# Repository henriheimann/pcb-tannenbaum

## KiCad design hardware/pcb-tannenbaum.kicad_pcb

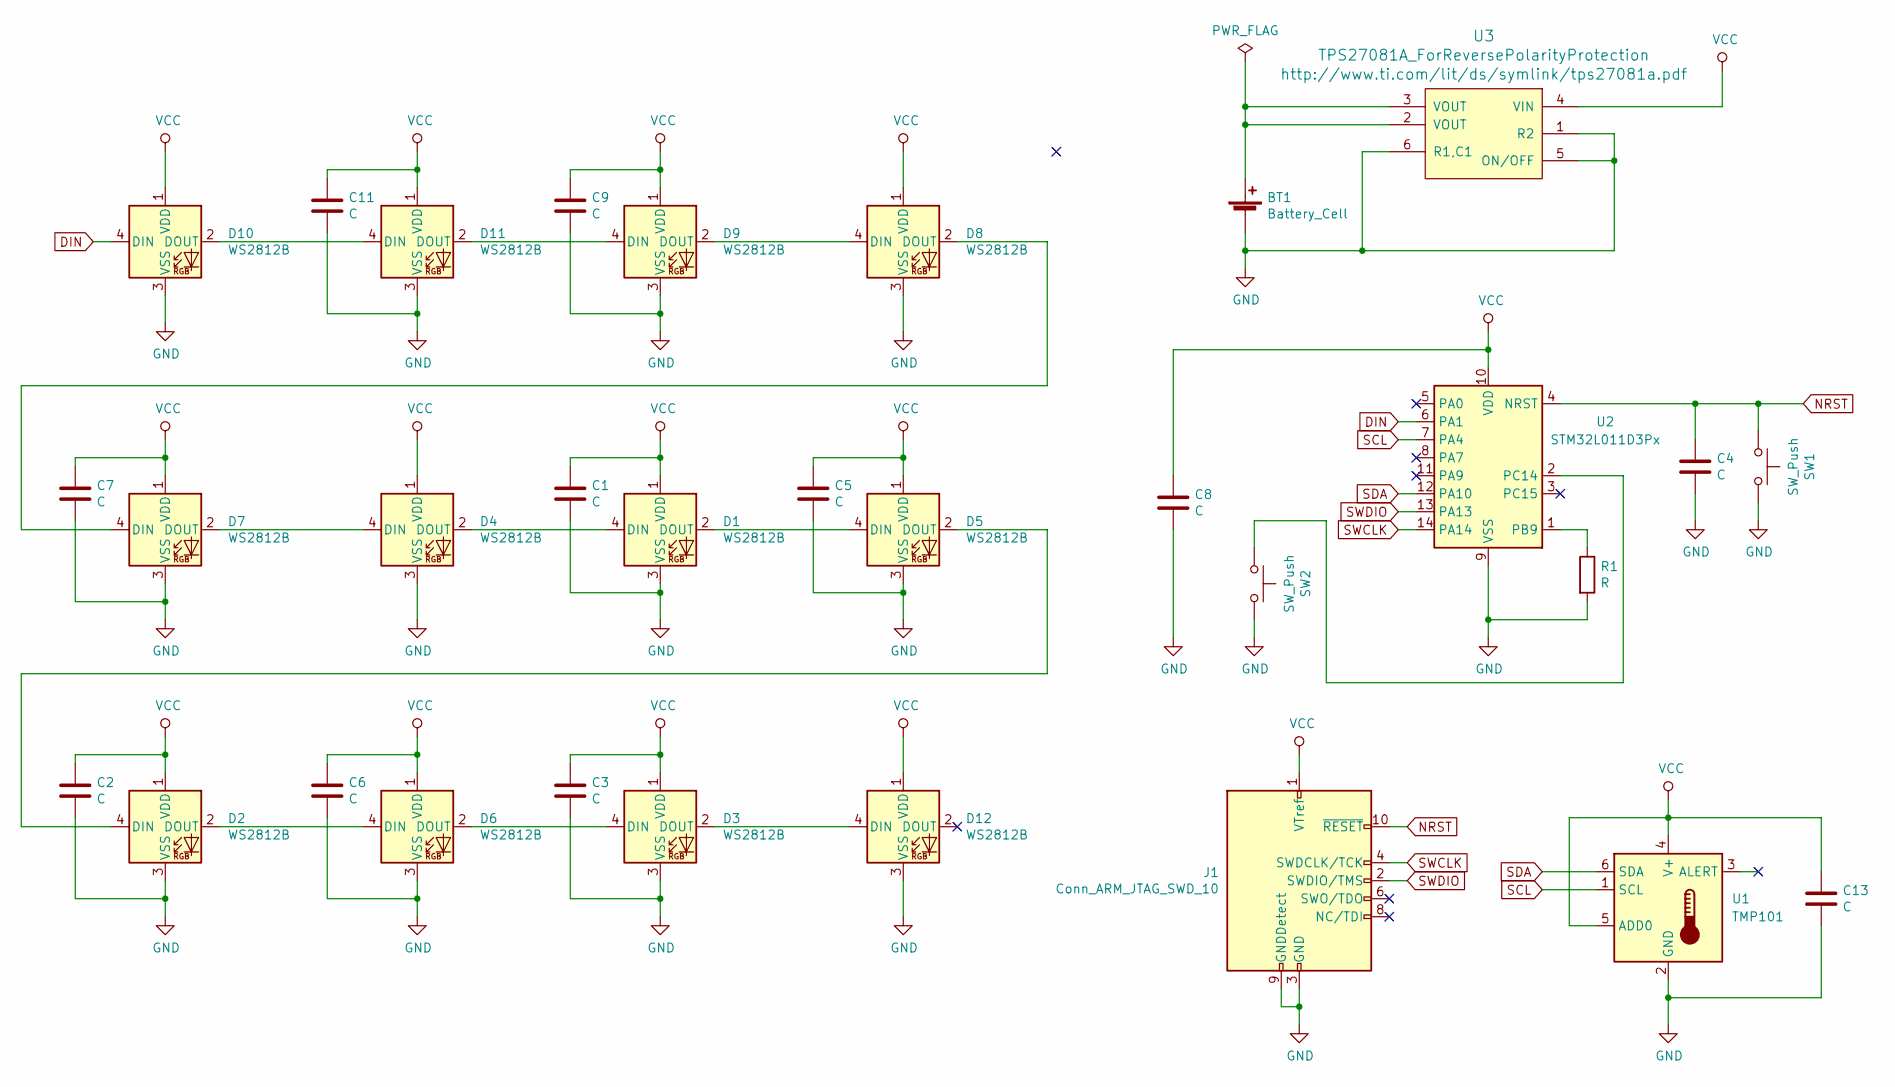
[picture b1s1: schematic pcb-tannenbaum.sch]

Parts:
BT1: Battery_Cell; BatteryHolder_Keystone_3034_1x20mm
C1, C2, C3, C4, C5, C6, C7, C8, C9, C11, C13: C; C_0805_2012Metric_Pad1.15x1.40mm_HandSolder
D1, D2, D3, D4, D5, D6, D7, D8, D9, D10, D11, D12: WS2812B; LED_WS2812B_PLCC4_5.0x5.0mm_P3.2mm_3DModel_NoSilk
J1: Conn_ARM_JTAG_SWD_10; PinHeader_2x05_P1.27mm_Vertical_SMD
R1: R; R_0805_2012Metric_Pad1.15x1.40mm_HandSolder
SW1, SW2: SW_Push; SW_Push_SPST_NO_Alps_SKRK
U1: TMP101; SOT-23-6
U2: STM32L011D3Px; TSSOP-14_4.4x5mm_P0.65mm
U3: TPS27081A_ForReversePolarityProtection; TSOT-23-6

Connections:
DIN: D10.4 (DIN), U2.6 (PA1)
GND: BT1.2 (-), C1.2, C2.2, C3.2, C4.2, C5.2, C6.2, C7.2, C8.2, C9.2, C11.2, C13.2, D1.3 (VSS), D2.3 (VSS), D3.3 (VSS), D4.3 (VSS), D5.3 (VSS), D6.3 (VSS), D7.3 (VSS), D8.3 (VSS), D9.3 (VSS), D10.3 (VSS), D11.3 (VSS), D12.3 (VSS), J1.3 (GND), J1.5 (GND), J1.9 (GNDDetect), R1.2, SW1.2, SW2.2, U1.2 (GND), U2.9 (VSS), U3.1 (R2), U3.5 (ON/OFF), U3.6 (R1,C1)
NRST: C4.1, J1.10 (~RESET~), SW1.1, U2.4 (NRST)
unnamed: BT1.1 (+), U3.2 (VOUT), U3.3 (VOUT)
unnamed: D1.2 (DOUT), D5.4 (DIN)
unnamed: D1.4 (DIN), D4.2 (DOUT)
unnamed: D2.2 (DOUT), D6.4 (DIN)
unnamed: D2.4 (DIN), D5.2 (DOUT)
unnamed: D3.4 (DIN), D6.2 (DOUT)
unnamed: D4.4 (DIN), D7.2 (DOUT)
unnamed: D7.4 (DIN), D8.2 (DOUT)
unnamed: D8.4 (DIN), D9.2 (DOUT)
unnamed: D10.2 (DOUT), D11.4 (DIN)
unnamed: D9.4 (DIN), D11.2 (DOUT)
unnamed: D3.2 (DOUT), D12.4 (DIN)
unnamed: R1.1, U2.1 (PB9)
unnamed: SW2.1, U2.2 (PC14)
SCL: U1.1 (SCL), U2.7 (PA4)
SDA: U1.6 (SDA), U2.12 (PA10)
SWCLK: J1.4 (SWDCLK/TCK), U2.14 (PA14)
SWDIO: J1.2 (SWDIO/TMS), U2.13 (PA13)
VCC: C1.1, C2.1, C3.1, C5.1, C6.1, C7.1, C8.1, C9.1, C11.1, C13.1, D1.1 (VDD), D2.1 (VDD), D3.1 (VDD), D4.1 (VDD), D5.1 (VDD), D6.1 (VDD), D7.1 (VDD), D8.1 (VDD), D9.1 (VDD), D10.1 (VDD), D11.1 (VDD), D12.1 (VDD), J1.1 (VTref), U1.4 (V+), U1.5 (ADD0), U2.10 (VDD), U3.4 (VIN)

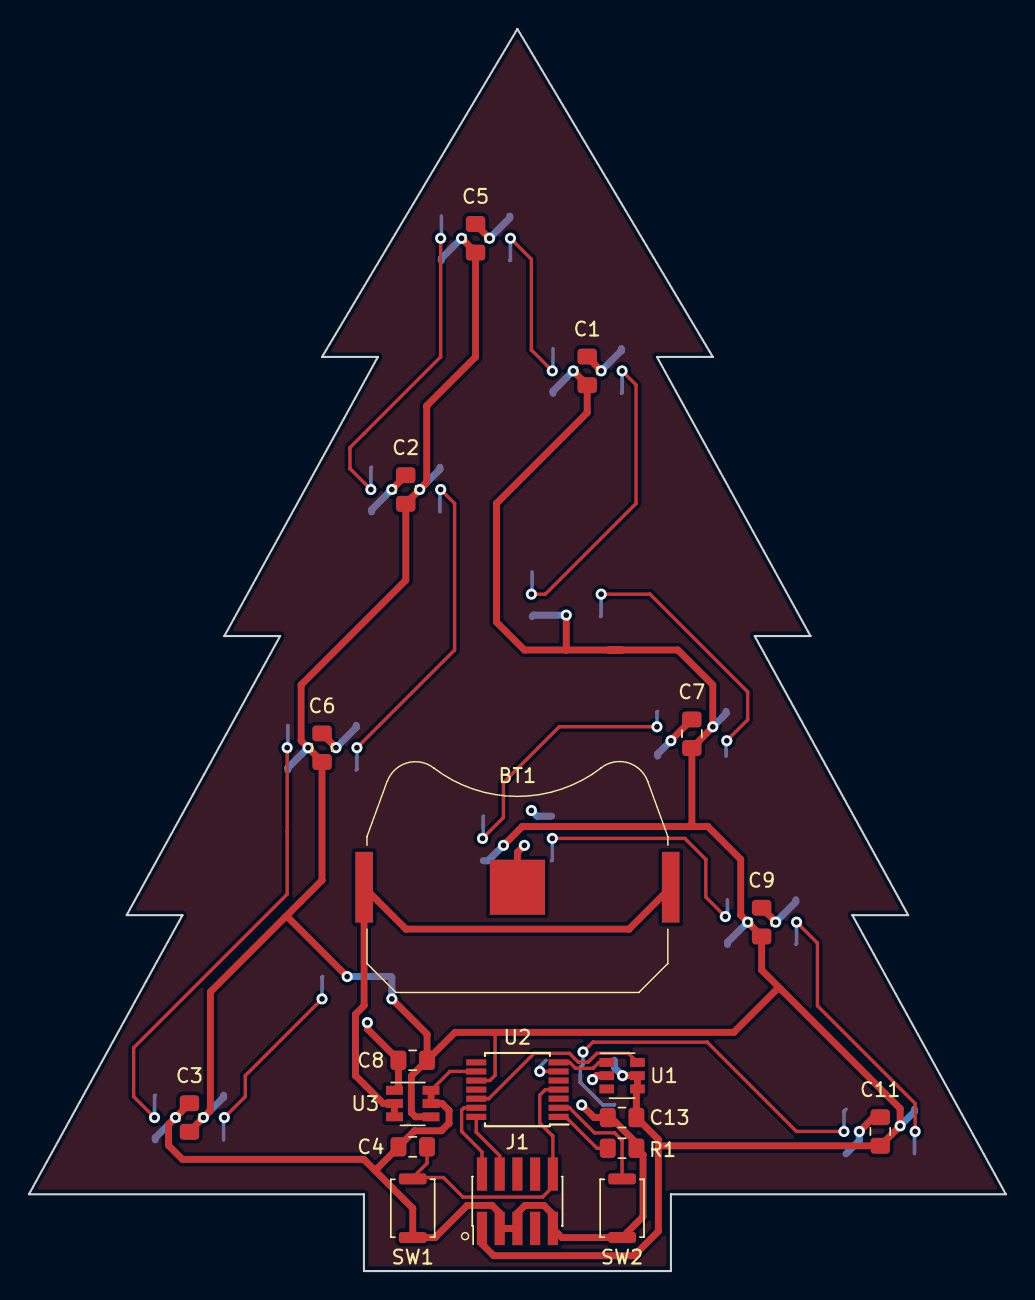
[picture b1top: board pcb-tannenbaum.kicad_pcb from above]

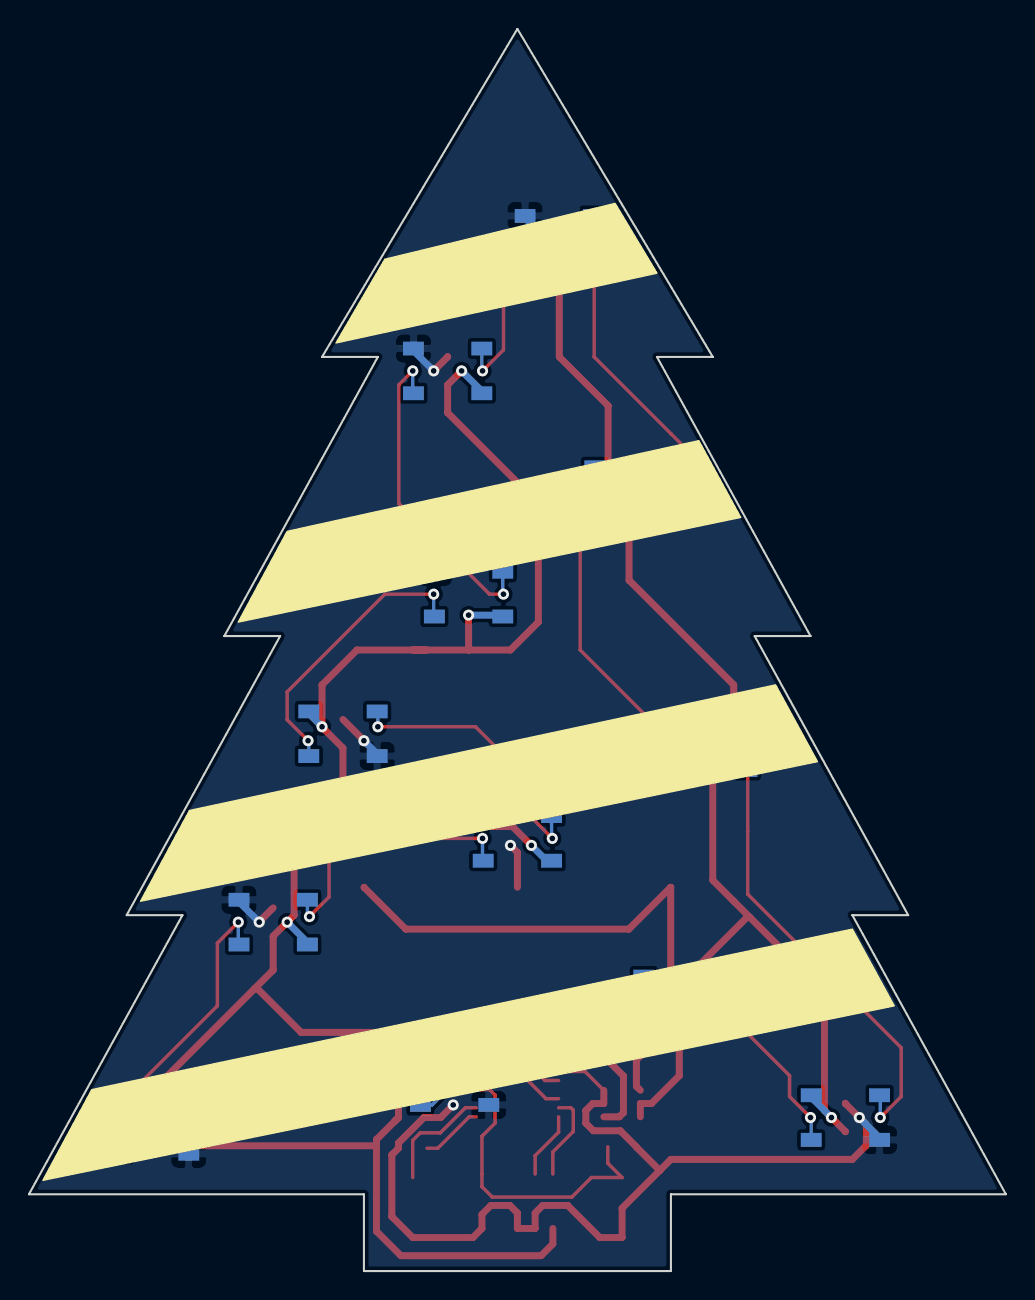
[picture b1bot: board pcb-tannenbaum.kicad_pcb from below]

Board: 2 copper layers, 70.0 x 89.0 mm, 31 parts (12 on the bottom side), 22 nets.

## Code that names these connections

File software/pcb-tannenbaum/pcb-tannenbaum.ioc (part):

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PA10.Mode=I2C
Mcu.UserName=STM32L011D3Px
PC14-OSC32_IN.Signal=GPXTI14
RCC.SYSCLKSource=RCC_SYSCLKSOURCE_PLLCLK
PA13.Signal=SYS_SWDIO
PA4.Mode=I2C
PA1.GPIO_PuPd=GPIO_PULLDOWN
PA1.Signal=S_TIM2_CH2
RCC.HSE_VALUE=8000000
board=custom
PC14-OSC32_IN.GPIO_ModeDefaultEXTI=GPIO_MODE_IT_FALLING
PA1.GPIOParameters=GPIO_PuPd,GPIO_Label
PA14.Mode=Serial_Wire
PA1.GPIO_Label=WS2812B
PA13.Mode=Serial_Wire
Mcu.Name=STM32L011D(3-4)Px
PC14-OSC32_IN.GPIOParameters=GPIO_PuPd,GPIO_Label,GPIO_ModeDefaultEXTI
PA4.Signal=I2C1_SCL
RCC.SYSCLKFreq_VALUE=32000000
Mcu.Package=TSSOP14
PA10.Signal=I2C1_SDA
PA14.Signal=SYS_SWCLK
PC14-OSC32_IN.GPIO_PuPd=GPIO_PULLUP
PC14-OSC32_IN.GPIO_Label=USER_BUTTON

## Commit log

2020-11-25 Finish first iteration of PCB layout
2020-11-25 Switch to STM MCU
2020-11-26 Remove rescue library
2020-11-30 Add cube project, change buttons
2020-12-10 Add initial code commit
2020-12-10 Use lowlevel library for RCC, finish tmp101 driver
2020-12-13 Implement WS2812B animation
2020-12-21 Switch to LL libraries
2020-12-21 Fix PWM generation
2020-12-21 User button as interrupt, check input voltage before enabling blue leds
2020-12-21 ADC initialization
2020-12-21 Fix tmp101 i2c transfers
2020-12-21 Remove ADC
2020-12-23 Add one shot conversion and i2c timeouts to tmp101
2020-12-23 Add PVD detector code
